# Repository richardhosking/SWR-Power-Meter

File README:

Driving the MCOB128064JX OLED Display
There is a datasheet at  https://midasdisplays.com/wp-content/uploads/2023/08/MCOB128064JX-YM.pdf

However it gives limited data as to drive the display in various interface formats 
For I2C 

(1) Set jumpers JB1 High
                JB2 Low 
(2) Pin 1 VCC 
    Pin 2 GND 
    Pin 4 SCL 
    Pin 5 SDA 
    Pin 12 Chip Select (Low)
    Pin 14 Reset (Low)
    Pin 16 High - read data from Display, Low - Command to display
    Pin 6-11 parallel data - grounded

(3) Set I2C address (J1C ? Open)
    0x3C // 011110+SA0+RW - 0x3C or 0x3D     

Library has constructors for I2C, Software SPI , Hardware SPI 
Using I2C in this case

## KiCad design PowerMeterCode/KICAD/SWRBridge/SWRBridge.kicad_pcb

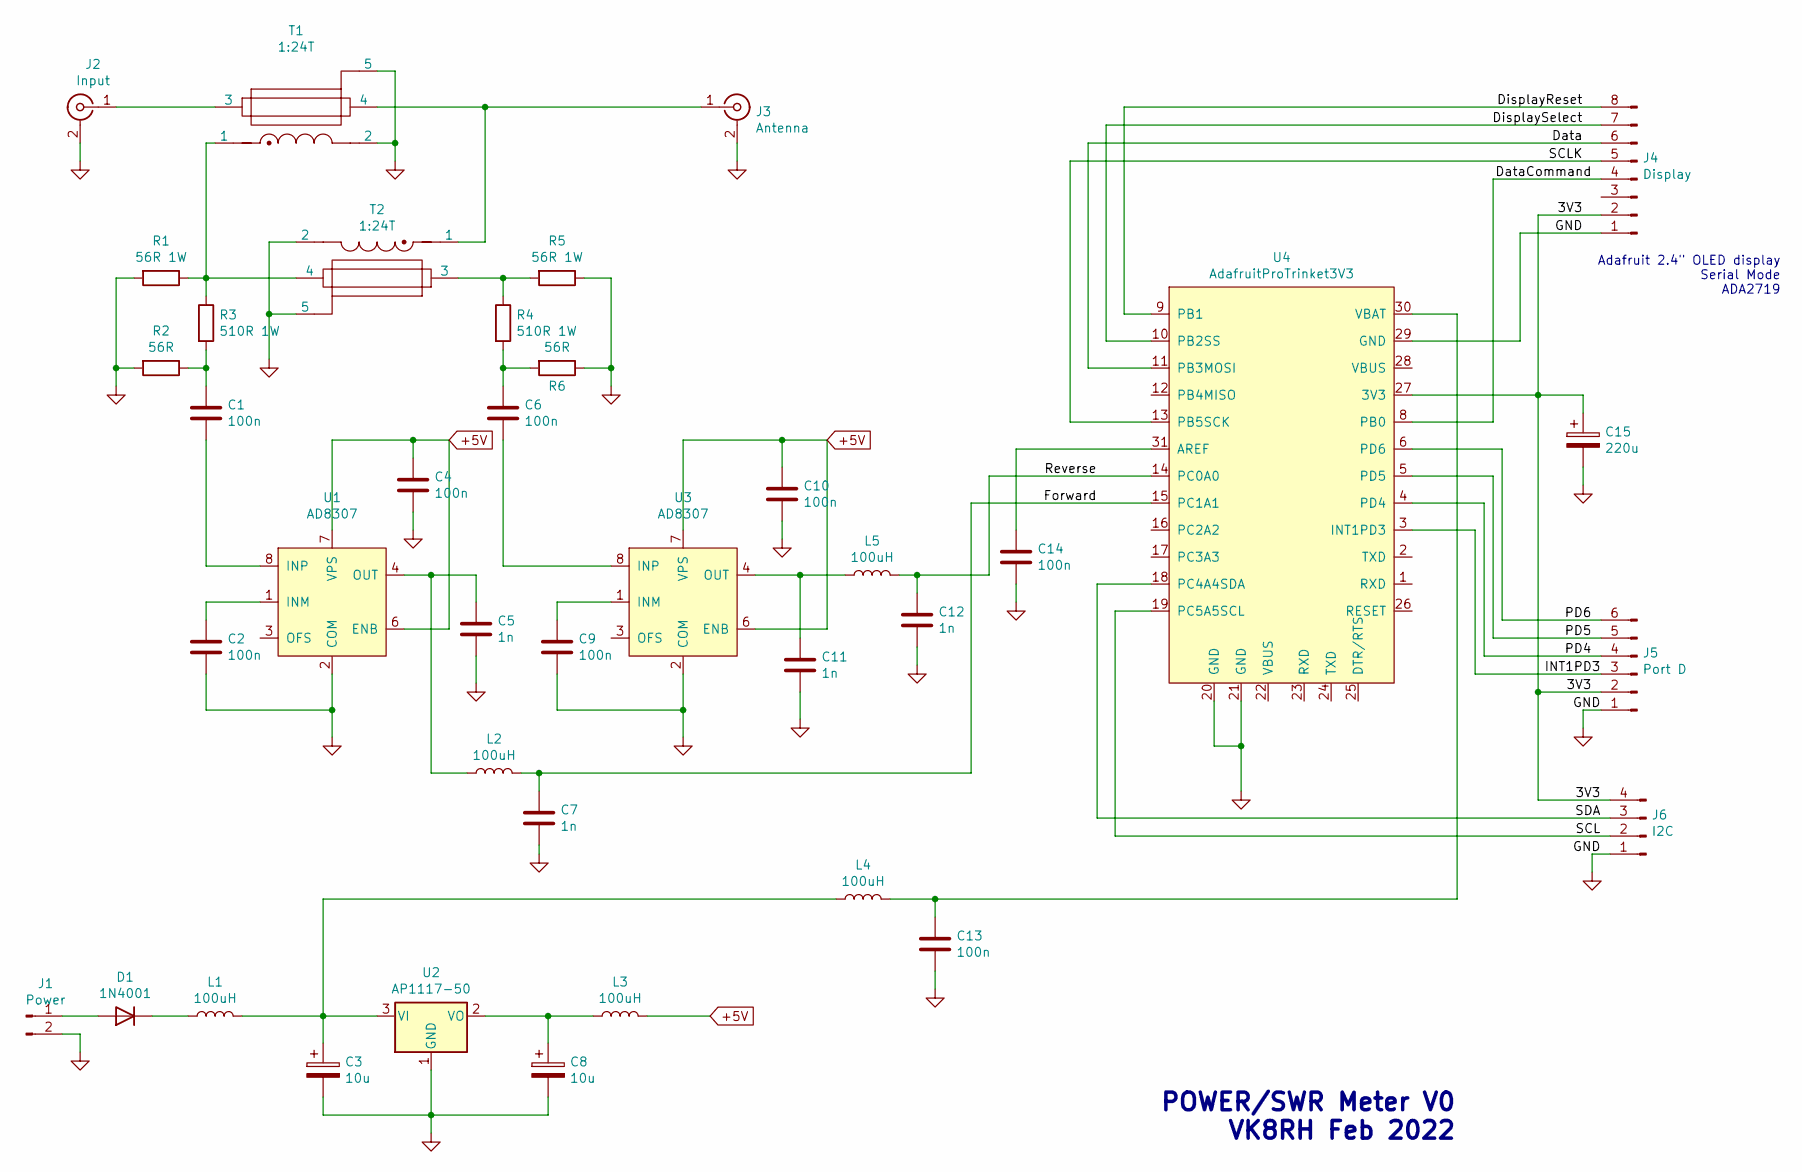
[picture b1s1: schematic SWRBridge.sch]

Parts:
C1, C2, C4, C6, C9, C10, C13, C14: 100n; C_1206_3216Metric_Pad1.33x1.80mm_HandSolder
C3, C8: 10u; CP_Elec_4x5.4
C5, C7, C11, C12: 1n; C_1206_3216Metric_Pad1.33x1.80mm_HandSolder
C15: 220u; CP_Elec_10x10
D1: 1N4001; D_1206_3216Metric_Pad1.42x1.75mm_HandSolder
J1: Power; PinHeader_1x02_P2.54mm_Vertical
J2: Input; Pad
J3: Antenna; Pad
J4: Display; PinHeader_1x08_P2.54mm_Vertical
J5: Port D; PinHeader_1x06_P2.54mm_Vertical
J6: I2C; PinHeader_1x04_P2.54mm_Vertical
L1, L2, L3, L4, L5: 100uH; L_1206_3216Metric_Pad1.42x1.75mm_HandSolder
R1, R5: 56R 1W; R_2512_6332Metric_Pad1.40x3.35mm_HandSolder
R2, R6: 56R; R_1206_3216Metric_Pad1.30x1.75mm_HandSolder
R3, R4: 510R 1W; R_2512_6332Metric_Pad1.40x3.35mm_HandSolder
T1, T2: 1:24T; SWRVoltageTransformer
U1, U3: AD8307; SO-8_3.9x4.9mm_P1.27mm
U2: AP1117-50; SOT-223-3_TabPin2
U4: AdafruitProTrinket3V3; AdafruitTrinketPro3V3

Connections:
+5V: C4.1, C10.1, L3.2, U1.6 (ENB), U1.7 (VPS), U3.6 (ENB), U3.7 (VPS)
/3V3: C15.1, J4.2, J5.2, J6.4, U4.27 (3V3)
/Data: J4.6, U4.11 (PB3MOSI)
/DataCommand: J4.4, U4.8 (PB0)
/DisplayReset: J4.8, U4.9 (PB1)
/DisplaySelect: J4.7, U4.10 (PB2SS)
/Forward: C7.1, L2.2, U4.15 (PC1A1)
/INT1PD3: J5.3, U4.3 (INT1PD3)
/PD4: J5.4, U4.4 (PD4)
/PD5: J5.5, U4.5 (PD5)
/PD6: J5.6, U4.6 (PD6)
/Reverse: C12.1, L5.2, U4.14 (PC0A0)
/SCL: J6.2, U4.19 (PC5A5SCL)
/SCLK: J4.5, U4.13 (PB5SCK)
/SDA: J6.3, U4.18 (PC4A4SDA)
GND: C2.2, C3.2, C4.2, C5.2, C7.2, C8.2, C9.2, C10.2, C11.2, C12.2, C13.2, C14.2, C15.2, J1.2, J2.2 (Ext), J3.2 (Ext), J4.1, J5.1, J6.1, R1.2, R2.2, R5.1, R6.1, T1.2, T1.5, T2.2, T2.5, U1.2 (COM), U2.1 (GND), U3.2 (COM), U4.20 (GND), U4.21 (GND), U4.29 (GND)
unnamed: C1.1, R2.1, R3.2
unnamed: C1.2, U1.8 (INP)
unnamed: C2.1, U1.1 (INM)
unnamed: C3.1, L1.2, L4.1, U2.3 (VI)
unnamed: C5.1, L2.1, U1.4 (OUT)
unnamed: C6.1, R4.2, R6.2
unnamed: C6.2, U3.8 (INP)
unnamed: C8.1, L3.1, U2.2 (VO)
unnamed: C9.1, U3.1 (INM)
unnamed: C11.1, L5.1, U3.4 (OUT)
unnamed: C13.1, L4.2, U4.30 (VBAT)
unnamed: C14.1, U4.31 (AREF)
unnamed: D1.1 (K), L1.1
unnamed: D1.2 (A), J1.1
unnamed: J2.1 (In), T1.3
unnamed: J3.1 (In), T1.4, T2.1
unnamed: R1.1, R3.1, T1.1, T2.4
unnamed: R4.1, R5.2, T2.3

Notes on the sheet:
Adafruit 2.4" OLED display Serial Mode ADA2719
POWER/SWR Meter V0 VK8RH Feb 2022

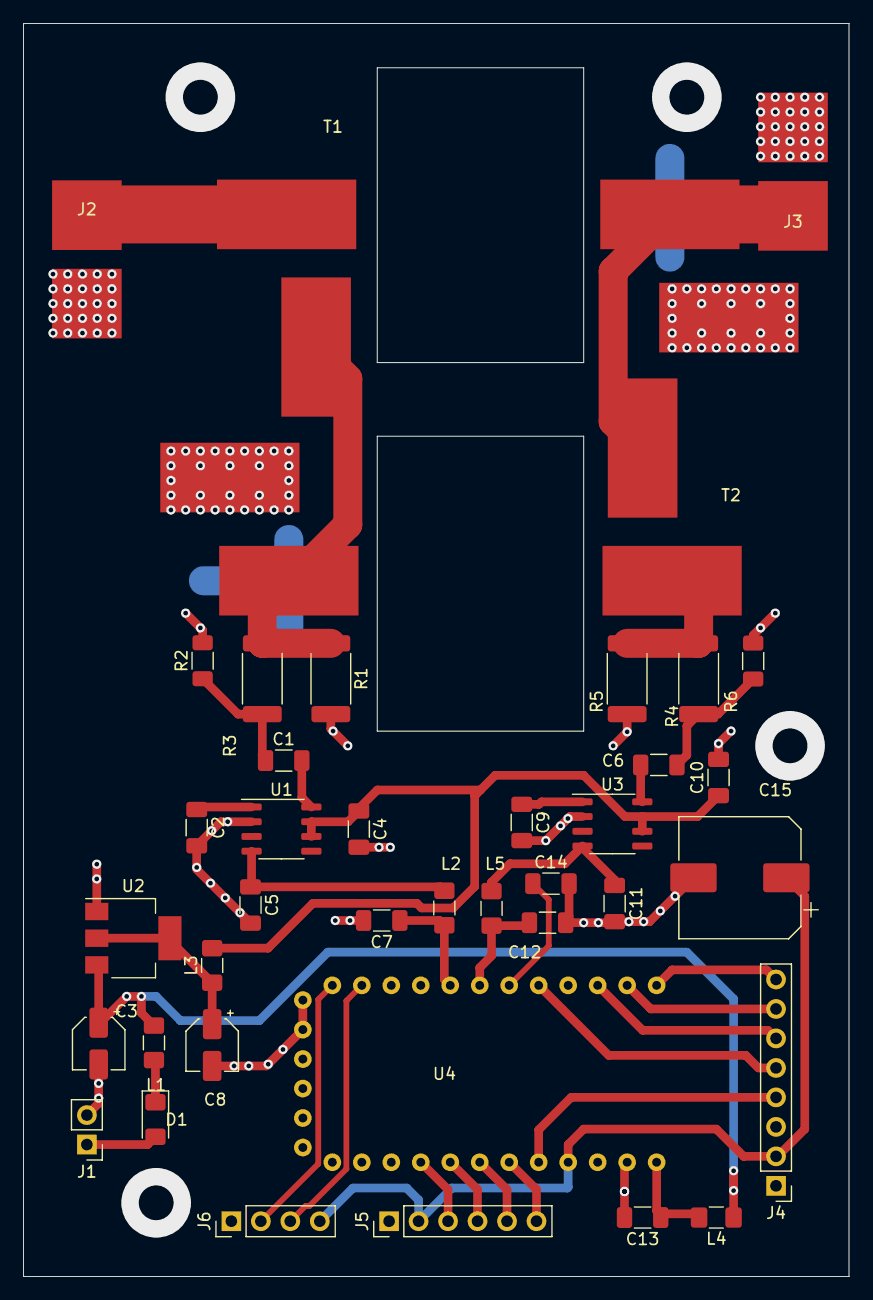
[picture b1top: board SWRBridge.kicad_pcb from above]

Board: 2 copper layers, 71.1 x 108.0 mm, 39 parts (0 on the bottom side), 34 nets.

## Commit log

2022-04-26 Update README.md
    Spelling corrections
2024-07-09 Delete PowerMeterCode/KICAD/SWRBridge directory
    Move KICAD to separate Repo
2024-11-21 ADS1115 added
2024-11-21 Update README.md
    Details of ADC and OLED
2024-11-21 Tidy up
2024-11-21 Update README.md
    Address for KICAD files
2025-01-14 Typo README.md
